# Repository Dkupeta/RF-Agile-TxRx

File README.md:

# RF-Agile-TxRx
AD9361 based Agile Transceiver

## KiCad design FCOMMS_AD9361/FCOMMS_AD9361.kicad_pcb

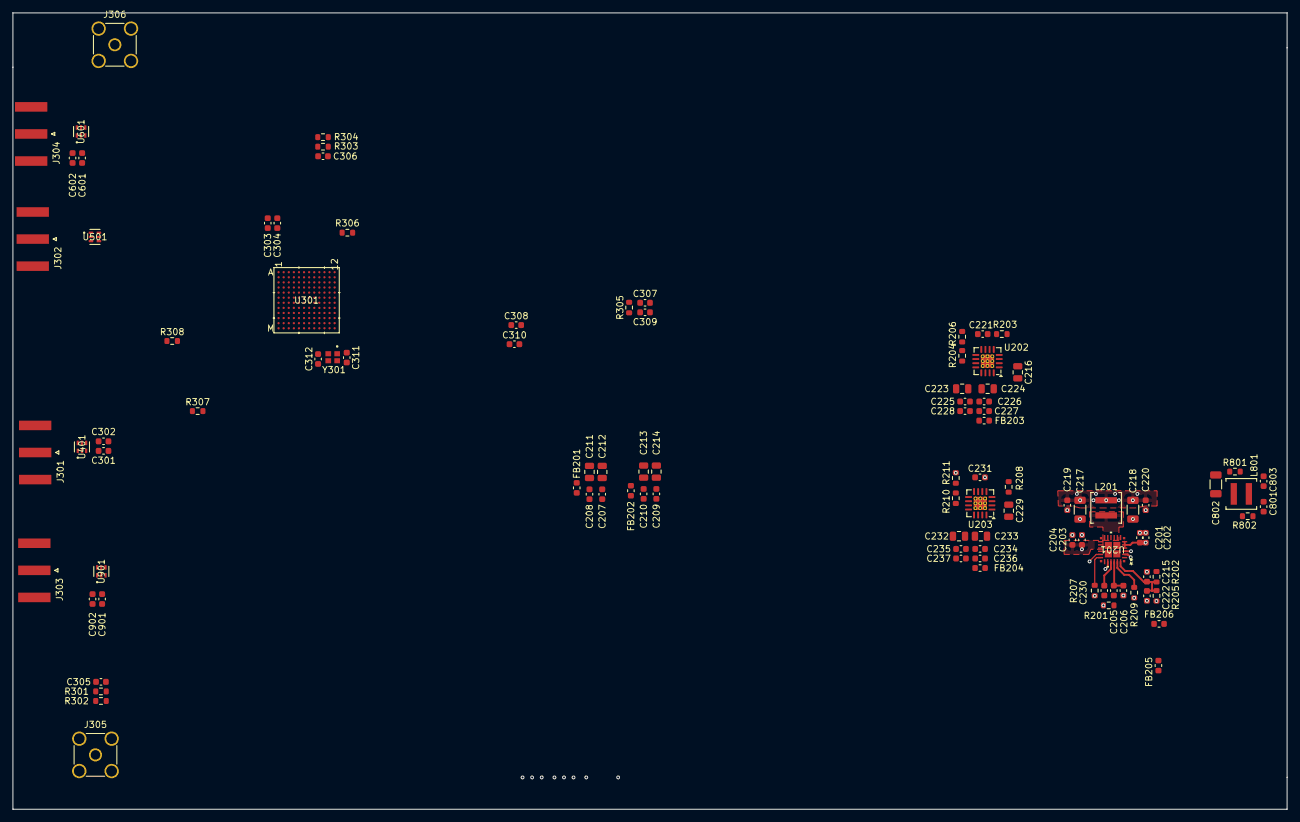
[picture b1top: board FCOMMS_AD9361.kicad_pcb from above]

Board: 8 copper layers, 200.0 x 125.0 mm, 100 parts (0 on the bottom side), 62 nets.

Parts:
C201, C203: 0.33µF; C_0603_1608Metric
C202, C204: 22µF; C_0603_1608Metric
C205: 8200pF; C_0603_1608Metric
C206: 750pF; C_0603_1608Metric
C207, C208, C209, C210, C309, C310: 1µF; C_0603_1608Metric
C211, C212, C213, C214: 0.01µF; C_0805_2012Metric
C215, C222: C; C_0603_1608Metric
C216, C223, C224, C229, C232, C233: 4.7uF; C_0805_2012Metric
C217, C218: 100µF; C_1206_3216Metric
C219, C220: 0.15µF; C_0603_1608Metric
C221, C230, C231, C305, C306: 1nF; C_0603_1608Metric
C225, C226, C228, C234, C235, C236, C237: 0.1 µF; C_0603_1608Metric
C227: 0.1µF; C_0603_1608Metric
C301, C302, C303, C304: 18pF; C_0603_1608Metric
C307, C308, C601, C901: 0.001µF; C_0603_1608Metric
C311: 12pF; C_0603_1608Metric
C312: 12 pF; C_0603_1608Metric
C602, C902: 10 µF; C_0603_1608Metric
C801, C803: 22uF; C_0603_1608Metric
C802: 68uF; C_1206_3216Metric
FB201, FB206: 75 Ohms @ 100 MHz; L_0603_1608Metric
FB202, FB203, FB204, FB205: 30 Ohms @ 100 MHz; L_0603_1608Metric
J301, J302, J303, J304: Conn_Coaxial; SMA_Amphenol_132289_EdgeMount
J305, J306: Conn_Coaxial; SMA_Amphenol_901-144_Vertical
L201: 270nH; L_Coilcraft_XAL4040-XXX
L801: 760 nH; L_Coilcraft_XAL4030-XXX
R201: 3.01k; R_0603_1608Metric
R202: 60.4k; R_0603_1608Metric
R203, R207, R208, R209: 100k; R_0603_1608Metric
R204, R210: 16K; R_0603_1608Metric
R205: 30.1k; R_0603_1608Metric
R206, R211: 10K; R_0603_1608Metric
R301, R303, R801, R802: 10; R_0603_1608Metric
R302, R304: 49R9; R_0603_1608Metric
R305, R306: 1; R_0603_1608Metric
R307: 10k; R_0603_1608Metric
R308: 14.3k 1%; R_0603_1608Metric
U201: LT8644SIV-TRMPBF; LQFN24_4X4X0.95_ADI
U202, U203: ADP1755ACPZ-R7; Analog_LFCSP-16-1EP_4x4mm_P0.65mm_EP2.1x2.1mm_ThermalVias
U301: AD9361BBCZ; BC_144_7_ADI
U401, U501, U601, U901: 2450BL15B050E; 2450BL15B050E_JOT
Y301: 402F4001XIAR; XTAL_402F4001XIAR

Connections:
/POWER/1V3A: C223.1, C224.1, C225.1, C226.1, C227.1, C228.1, FB204.2, R204.1, U202.10 (VOUT), U202.11 (VOUT), U202.12 (VOUT), U202.13 (VOUT), U202.14 (VOUT)
/POWER/1V3B: C232.1, C233.1, C234.1, C235.1, C236.1, C237.1, FB205.2, R210.1, U203.10 (VOUT), U203.11 (VOUT), U203.12 (VOUT), U203.13 (VOUT), U203.14 (VOUT)
/POWER/Fb: C215.2, C222.1, R202.2, R205.1, U201.24 (FB)
/POWER/PG1: R203.2, U202.5 (PG)
/POWER/PG2: R208.2, U203.5 (PG)
/POWER/Pg: R209.1, U201.23 (PG)
/POWER/Rt: R207.1, U201.18 (RT)
/POWER/SW: L201.2, U201.8 (SW), U201.9 (SW), U201.10 (SW), U201.11 (SW), U201.12 (SW)
/POWER/Sync: U201.2 (INTVCC), U201.20 (SYNC/MODE)
/POWER/Vc: C205.1, C206.1, U201.22 (VC)
/POWER/Vdd_GPO: C207.1, C208.1, C211.1, C212.1, FB201.1
/POWER/Vdd_Interface: C209.1, C210.1, C213.1, C214.1, FB202.1
/POWER/Vf: C201.1, C202.1, C203.1, C204.1, C802.1, FB201.2, L801.2, U201.4 (SVIN), U201.5 (PVIN), U201.6 (PVIN), U201.13 (PVIN), U201.14 (PVIN), U201.15 (PVIN), U201.17 (EN/UB)
/POWER/Vin: C801.1, C803.1, L801.1
/POWER/Vout: C215.1, C217.1, C218.1, C219.1, C220.1, FB202.2, FB203.1, L201.1, R202.1, R209.2
/POWER/VoutX: C216.1, C229.1, FB203.2, R203.1, R208.1, U202.1 (VIN), U202.2 (VIN), U202.3 (VIN), U202.4 (EN), U202.15 (VIN), U202.16 (VIN), U203.1 (VIN), U203.2 (VIN), U203.3 (VIN), U203.4 (EN), U203.15 (VIN), U203.16 (VIN)
/POWER/ss: C230.1, U201.21 (SS)
/RF/1P3_TX1A: C901.1, C902.1, U301.M9 (TX1B_P), U301.M10 (TX1B_N), U901.2 (GND/DC-FEED)
/RF/1P3_TX2A: C601.1, C602.1, U301.A9 (TX2B_N), U301.A10 (TX2B_P), U601.2 (GND/DC-FEED)
/RF/RX1A: J301.1 (In), U401.1 (UNBALANCED-PORT)
/RF/RX1A_N: C301.2, U301.M2 (RX1A_N)
/RF/RX1A_P: C302.2, U301.M1 (RX1A_P)
/RF/RX2A: J302.1 (In), U501.1 (UNBALANCED-PORT)
/RF/RX2A_N: C303.2, U301.A1 (RX2A_N)
/RF/RX2A_P: C304.2, U301.A2 (RX2A_P)
/RF/SMA1/BAL_OUT1: C303.1, U501.3 (BALANCED-PORT)
/RF/SMA1/BAL_OUT2: C304.1, U501.4 (BALANCED-PORT)
/RF/SMA/BAL_OUT1: C301.1, U401.3 (BALANCED-PORT)
/RF/SMA/BAL_OUT2: C302.1, U401.4 (BALANCED-PORT)
/RF/TX1A: J303.1 (In), U901.1 (UNBALANCED-PORT)
/RF/TX1A_N: U301.M8 (TX1A_N), U901.3 (BALANCED-PORT)
/RF/TX1A_P: U301.M7 (TX1A_P), U901.4 (BALANCED-PORT)
/RF/TX2A: J304.1 (In), U601.1 (UNBALANCED-PORT)
/RF/TX2A_N: U301.A7 (TX2A_N), U601.3 (BALANCED-PORT)
/RF/TX2A_P: U301.A8 (TX2A_P), U601.4 (BALANCED-PORT)
/RF/TXM1: J305.1 (In), R301.1, R302.2
/RF/TXM2: J306.1 (In), R303.1, R304.2
/RF/TX_MON1: C305.2, U301.M5 (TX_MON1)
/RF/TX_MON2: C306.2, U301.A5 (TX_MON2)
/RF/Vdd_Interface: R307.2, U301.H12 (VDD_INTERFACE)
/RF/Vdd_RX_LO: U301.E2 (VDDA1P3_RX_LO), U301.F2 (VDDA1P3_RX_VCO_LDO)
/RF/Vdd_RX_TX: U301.D2 (VDDA1P3_RX_RF), U301.D3 (VDDA1P3_RX_TX), U301.E3 (VDDA1P3_TX_LO_BUFFER)
/RF/Vdd_RX_VCO: C307.1, R305.2, U301.G2 (RX_VCO_LDO_OUT), U301.G3 (VDDA1P1_RX_VCO)
/RF/Vdd_TX_LO: U301.B9 (VDDA1P3_TX_LO), U301.B10 (VDDA1P3_TX_VCO_LDO)
/RF/Vdd_TX_VCO: C308.1, R306.2, U301.A11 (VDDA1P1_TX_VCO), U301.B11 (TX_VCO_LDO_OUT)
AGND: C206.2, C222.2, C230.2, FB206.2, R201.2, R205.2, R207.2, U201.3 (AGND)
GND: C201.2, C202.2, C203.2, C204.2, C207.2, C208.2, C209.2, C210.2, C211.2, C212.2, C213.2, C214.2, C216.2, C217.2, C218.2, C219.2, C220.2, C221.2, C223.2, C224.2, C225.2, C226.2, C227.2, C228.2, C229.2, C231.2, C232.2, C233.2, C234.2, C235.2, C236.2, C237.2, C307.2, C308.2, C309.2, C310.2, C311.2, C312.2, C601.2, C602.2, C803.2, C901.2, C902.2, FB206.1, J301.2 (Ext), J302.2 (Ext), J303.2 (Ext), J304.2 (Ext), J305.2 (Ext), J306.2 (Ext), R206.2, R211.2, R302.1, R304.1, R308.1, R801.2, R802.2, U201.16 (PGND), U201.25 (PGND), U201.26 (PGND), U201.27 (PGND), U201.28 (PGND), U201.29 (GND), U201.30 (GND), U201.31 (GND), U201.32 (GND), U202.6 (GND), U202.17 (EPAD), U203.6 (GND), U203.17 (EPAD), U301.A4 (VSSA), U301.A6 (VSSA), U301.B1 (VSSA), U301.B2 (VSSA), U301.B12 (VSSA), U301.C1 (RX2C_P), U301.C2 (VSSA), U301.C4 (TEST/ENABLE), U301.C7 (VSSA), U301.C8 (VSSA), U301.C9 (VSSA), U301.C10 (VSSA), U301.C11 (VSSA), U301.C12 (VSSA), U301.D1 (RX2C_N), U301.D12 (VSSD), U301.E1 (RX2B_P), U301.F1 (RX2B_N), U301.F3 (VSSA), U301.F7 (VSSD), U301.F9 (VSSD), U301.F11 (VSSD), U301.G12 (VSSD), U301.H1 (RX1B_P), U301.H2 (VSSA), U301.H3 (VSSA), U301.H6 (VSSA), U301.H7 (VSSD), U301.H10 (VSSD), U301.J1 (RX1B_N), U301.J2 (VSSA), U301.K1 (RX1C_P), U301.K2 (VSSA), U301.K12 (VSSD), U301.L1 (RX1C_N), U301.L2 (VSSA), U301.L3 (VSSA), U301.L7 (VSSA), U301.L8 (VSSA), U301.L9 (VSSA), U301.L10 (VSSA), U301.L11 (VSSA), U301.L12 (VSSA), U301.M4 (VSSA), U301.M6 (VSSA), U401.2 (GND/DC-FEED), U401.5 (GND), U501.2 (GND/DC-FEED), U501.5 (GND), U601.5 (GND), U901.5 (GND), Y301.2 (GND), Y301.4 (GND__1)
unnamed: C205.2, R201.1
unnamed: C305.1, R301.2
unnamed: C306.1, R303.2
unnamed: C309.1, R305.1
unnamed: C310.1, R306.1
unnamed: C801.2, R802.1
unnamed: C802.2, R801.1
unnamed: R204.2, R206.1, U202.9 (ADJ)
unnamed: C221.1, U202.7 (SS)
unnamed: R210.2, R211.1, U203.9 (ADJ)
unnamed: C231.1, U203.7 (SS)
unnamed: R308.2, U301.L4 (RBIAS)
unnamed: R307.1, U301.K5 (RESETB)
unnamed: C311.1, U301.M12 (XTALN), Y301.1
unnamed: C312.1, U301.M11 (XTALP), Y301.3

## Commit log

2025-02-14 agile RF
2025-02-14 Add AD9361
2025-02-14 add vias to PCB
2025-02-14 add local library
2025-02-14 branch push001
2025-02-15 add mcu to design
2025-02-23 refresh on Ubuntu
